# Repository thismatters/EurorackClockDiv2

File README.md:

# Clock Divider (type 2)

```
      ----  ----  ----  ----  ----  ----  ----  ----  ----
IN    |  |  |  |  |  |  |  |  |  |  |  |  |  |  |  |  |  |
    ---  ----  ----  ----  ----  ----  ----  ----  ----  ---
      ----              ----              ----
OUT   |  |              |  |              |  |
n=3 ---  ----------------  ----------------  ---------------
```

This clock divider takes a regular clock signal and generates one pulse every `n` input steps. A knob allows you choose `n` between 1 and 10. Combine this with the [binary clock divider](https://www.github.com/thismatters/EurorackClockDiv/) in my series to generate many permutations on a clock signal.

The circuit here is based on the [Yusynth Clock Divider](https://yusynth.net/Modular/EN/DIVIDER/index.html) with minor tweaks to make it more Eurorack friendly. The changes I've made are thus:
* Selected resistors appropriate for +/-12V rails,
* Added polarity protection so that a backward power header doesn't fry anything (twin series schotty diodes: BAT54SL),
* Full surface mount design,
* More step options!

The Yusynth page is a treasure trove of information about this circuit that I am too amateur to claim as my own; please read that outstanding page before using this circuit. The page provides many details and other implementations of this circuit that you may find suitable.

The KiCAD project here uses the library/footprints [found in my companion repo](https://github.com/thismatters/EurorackKiCAD).

## Width

10hp on a 1u rack (Intellijel).

## Inputs

Jacks:
- Clock input*
- Reset gate

Knobs:
- 10 position switch for choosing the frequency of gate outputs

\* Note that this module requires a fairly clean input clock signal.

## Outputs

Gate output. LED indicator.

## Vendors

There are part numbers in the [BOM](clkdiv2.csv) for many of the parts (not for basic passives though) at the following vendors:

* [Mouser](https://www.mouser.com): Needs no introduction. Get your ICs from here (or [digikey](https://www.digikey.com)).
* [Tayda Electronics](https://www.taydaelectronics.com/): Good supplier for passive components; audio jacks, and potentiometers. Their audio jacks are slightly smaller than the thonkiconn from thonk.
* [Love My Switches](https://lovemyswitches.com/): Has [really good knobs](https://lovemyswitches.com/anodized-aluminum-knob-the-lo-fi-1-4-smooth-shaft-12-5mm-od/) to go on those potentiometers!
* [OSHPark](https://oshpark.com/): Fast and (relatively) cheap PCB manufacturer. [V0a works great!](https://oshpark.com/shared_projects/LyyWQIPF)

## Changelog

### V0a (Same solder paste stencil as V0 will work here)
- [x] Fixed wrong schematic symbol for dual transistor package (Q3 pinout didn't match the BCM847.)
- [x] Fixed LED footprint to correct side of the board
- [x] Fixed D9 screenprint overlap

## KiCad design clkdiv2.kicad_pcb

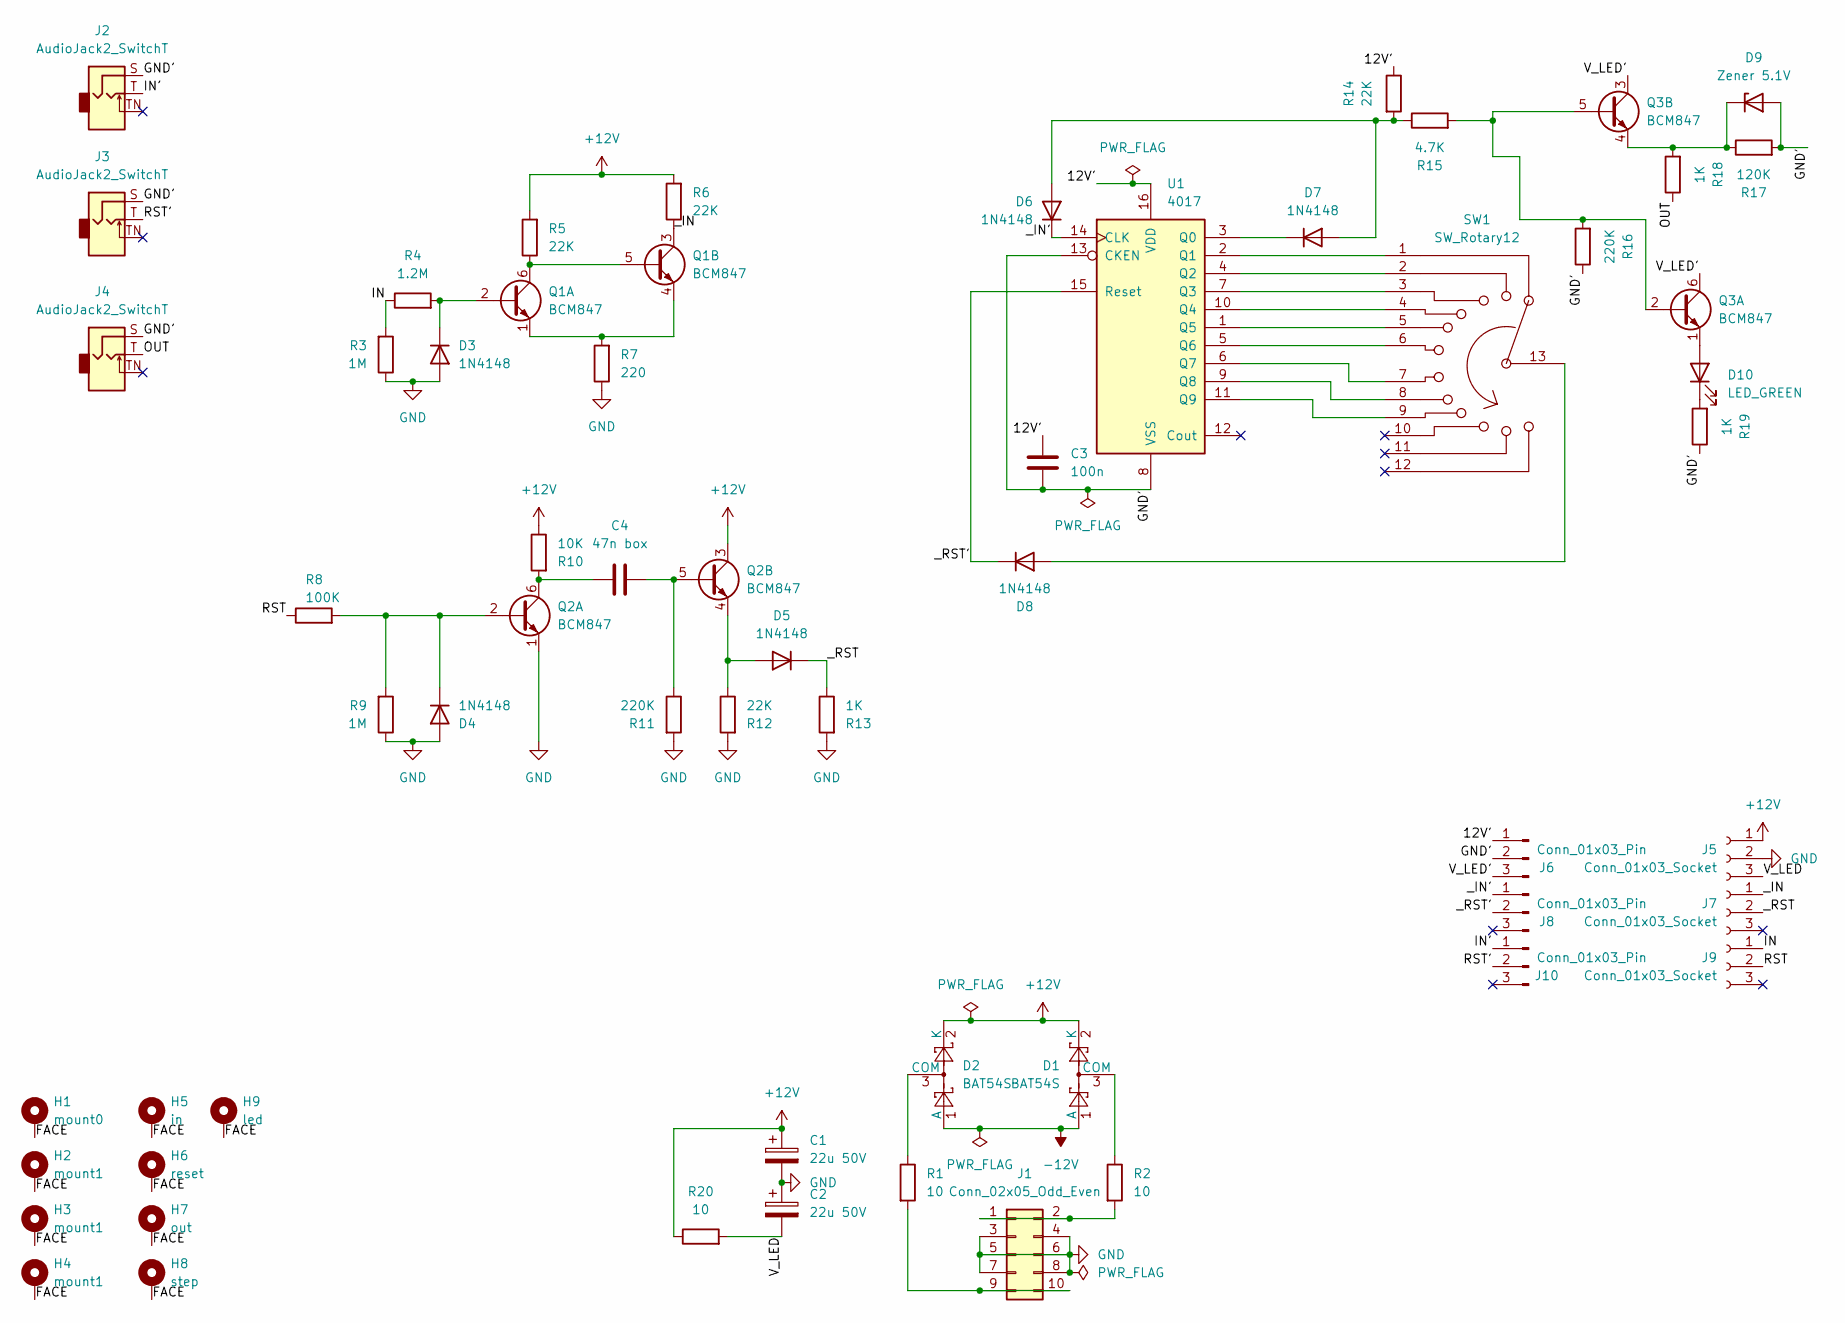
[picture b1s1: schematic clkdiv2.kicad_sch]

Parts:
C1, C2: 22u 50V; CP_Radial_D5.0mm_P2.50mm
C3: 100n; C_0805_2012Metric
C4: 47n box; C_Rect_L7.2mm_W2.5mm_P5.00mm_FKS2_FKP2_MKS2_MKP2
D1, D2: BAT54S; SOT-23; PartNum 863-BAT54SLT1G
D3, D4, D5, D6, D7, D8: 1N4148; D_SOD-323_HandSoldering
D9: Zener 5.1V; D_MiniMELF
D10: LED_GREEN; LED_D3.0mm
H1: mount0; Mech-MountingHole
H2, H3, H4: mount1; Mech-MountingHole
H5: in; Mech-AudioJack-Hole-Input-Clock
H6: reset; Mech-AudioJack-Hole-Input-Gate
H7: out; Mech-AudioJack-Hole-Output-Gate
H8: step; Mech-MRK-Hole
H9: led; Mech-LED-Hole-3mm-Bezel
J1: Conn_02x05_Odd_Even; PinHeader_2x05_P2.54mm_Vertical; PartNum A-2939
J2, J3, J4: AudioJack2_SwitchT; AudioJack2_Tayda_A-2566; PartNum A-2566
J5, J7, J9: Conn_01x03_Socket; PinSocket_1x03_P2.54mm_Vertical
J6, J8, J10: Conn_01x03_Pin; PinHeader_1x03_P2.54mm_Vertical
Q1, Q2, Q3: BCM847; TSOP-6_1.65x3.05mm_P0.95mm; PartNum 771-BCM847DS135
R1, R2, R20: 10; R_0805_2012Metric
R3, R9: 1M; R_0805_2012Metric
R4: 1.2M; R_0805_2012Metric
R5, R6, R12, R14: 22K; R_0805_2012Metric
R7: 220; R_0805_2012Metric
R8: 100K; R_0805_2012Metric
R10: 10K; R_0805_2012Metric
R11, R16: 220K; R_0805_2012Metric
R13, R18, R19: 1K; R_0805_2012Metric
R15: 4.7K; R_0805_2012Metric
R17: 120K; R_0805_2012Metric
SW1: SW_Rotary12; Switch_Rotary_NKK_MRK_112; PartNum 633-MRK112-BA
U1: 4017; TSSOP-16_4.4x5mm_P0.65mm; PartNum 595-CD4017BPWR

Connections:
+12V: C1.1, D1.2 (K), D2.2 (K), J5.1, Q2.3 (C2), R5.2, R6.2, R10.1, R20.1
-12V: D1.1 (A), D2.1 (A)
/12V': C3.1, J6.1, R14.1, U1.16 (VDD)
/FACE: H1.1, H2.1, H3.1, H4.1, H5.1, H6.1, H7.1, H8.1, H9.1
/GND': C3.2, D9.2 (A), J2.S, J3.S, J4.S, J6.2, R16.1, R17.2, R19.1, U1.8 (VSS), U1.13 (CKEN)
/IN: J9.1, R3.2, R4.1
/IN': J2.T, J10.1
/OUT: J4.T, R18.1
/RST: J9.2, R8.1
/RST': J3.T, J10.2
/V_LED: C2.2, J5.3, R20.2
/V_LED': J6.3, Q3.3 (C2), Q3.6 (C1)
/_IN: J7.1, Q1.3 (C2), R6.1
/_IN': D6.1 (K), J8.1, U1.14 (CLK)
/_RST: D5.1 (K), J7.2, R13.1
/_RST': D8.1 (K), J8.2, U1.15 (Reset)
GND: C1.2, C2.1, D3.2 (A), D4.2 (A), J1.3, J1.4, J1.5, J1.6, J1.7, J1.8, J5.2, Q2.1 (E1), R3.1, R7.1, R9.1, R11.2, R12.2, R13.2
unnamed: D1.3 (COM), R2.1
unnamed: D2.3 (COM), R1.1
unnamed: D3.1 (K), Q1.2 (B1), R4.2
unnamed: D4.1 (K), Q2.2 (B1), R8.2, R9.2
unnamed: D5.2 (A), Q2.4 (E2), R12.1
unnamed: D6.2 (A), D7.2 (A), R14.2, R15.1
unnamed: D7.1 (K), U1.3 (Q0)
unnamed: D8.2 (A), SW1.13
unnamed: D9.1 (K), Q3.4 (E2), R17.1, R18.2
unnamed: D10.2 (A), Q3.1 (E1)
unnamed: D10.1 (K), R19.2
unnamed: J1.1, J1.2, R2.2
unnamed: J1.9, J1.10, R1.2
unnamed: Q1.5 (B2), Q1.6 (C1), R5.1
unnamed: Q1.1 (E1), Q1.4 (E2), R7.2
unnamed: C4.1, Q2.6 (C1), R10.2
unnamed: C4.2, Q2.5 (B2), R11.1
unnamed: Q3.2 (B1), Q3.5 (B2), R15.2, R16.2
unnamed: SW1.1, U1.2 (Q1)
unnamed: SW1.2, U1.4 (Q2)
unnamed: SW1.3, U1.7 (Q3)
unnamed: SW1.4, U1.10 (Q4)
unnamed: SW1.5, U1.1 (Q5)
unnamed: SW1.6, U1.5 (Q6)
unnamed: SW1.7, U1.6 (Q7)
unnamed: SW1.8, U1.9 (Q8)
unnamed: SW1.9, U1.11 (Q9)

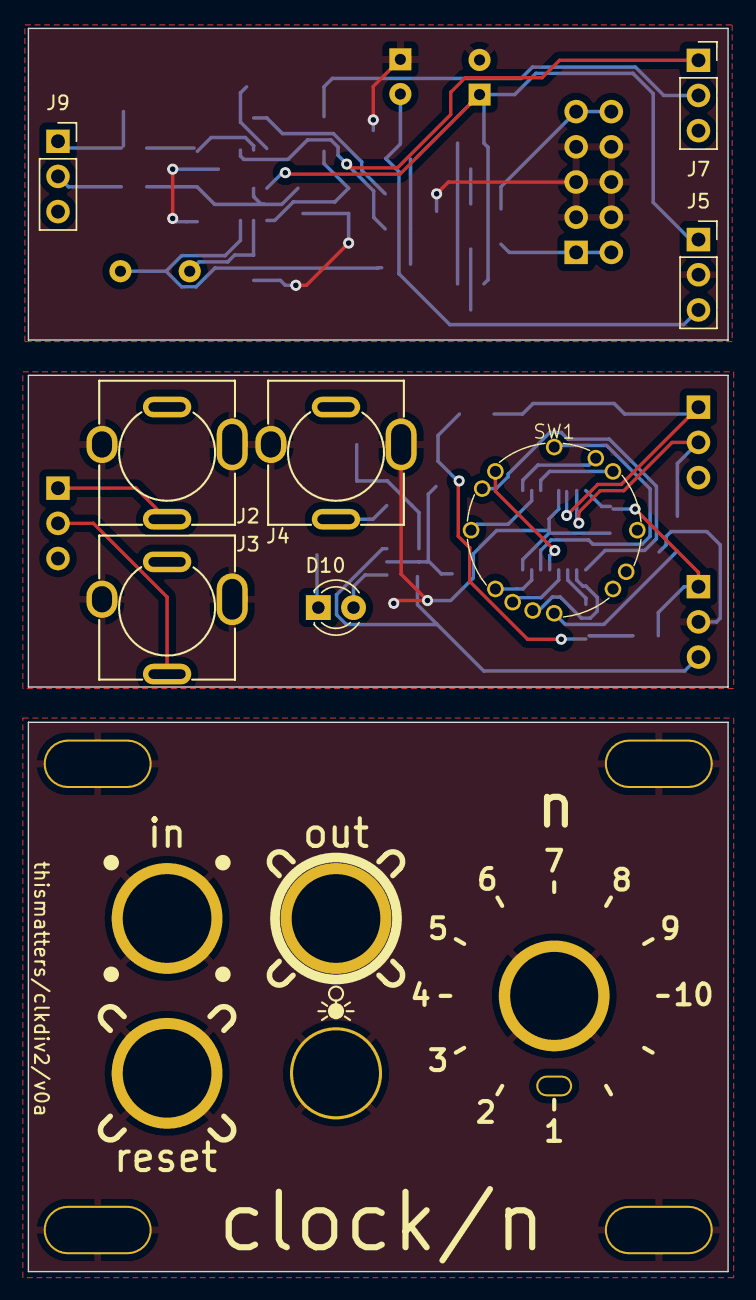
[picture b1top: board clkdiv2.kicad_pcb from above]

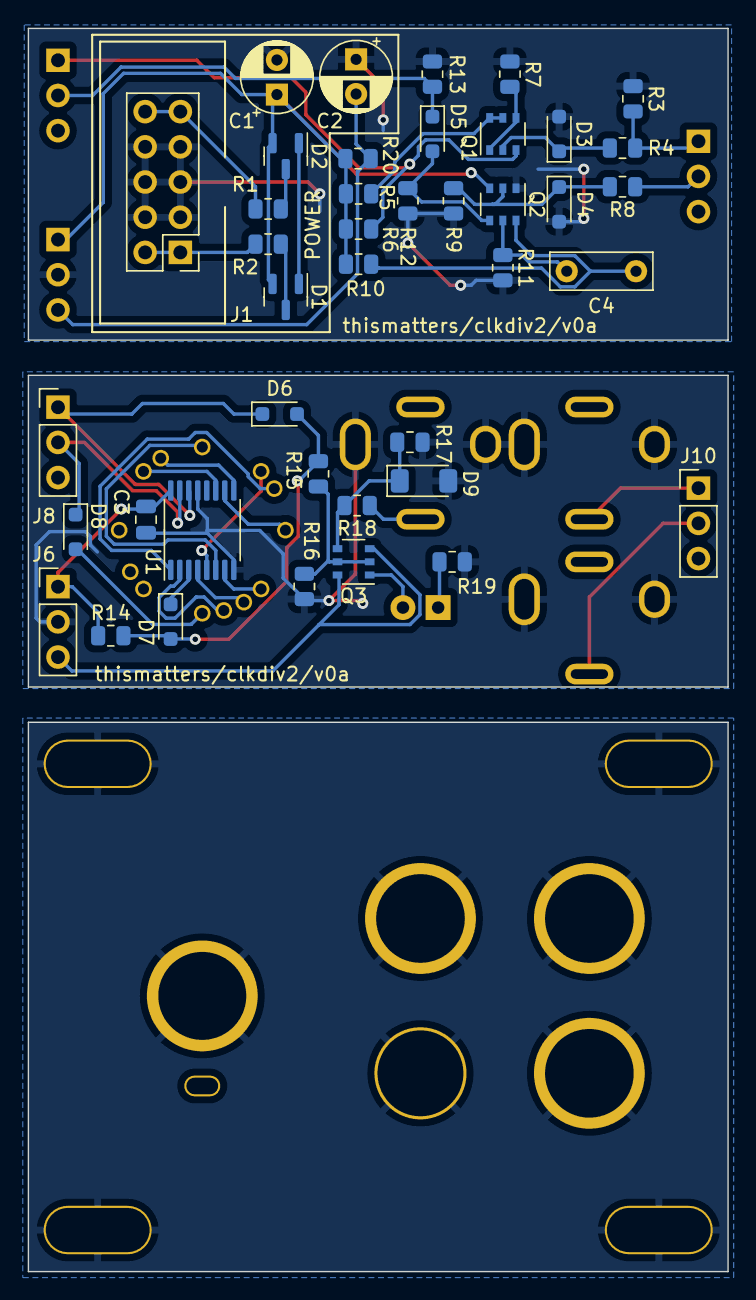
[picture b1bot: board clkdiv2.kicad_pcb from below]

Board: 2 copper layers, 50.5 x 89.7 mm, 58 parts (41 on the bottom side), 44 nets.

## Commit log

2024-11-30 initial commit, prebreadboard
2024-12-06 pcb ready for v0 manu
2025-01-11 pcb ready for v0a manu
2025-03-29 v0a built and working
